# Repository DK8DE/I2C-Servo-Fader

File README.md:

# I2C-Servo-Fader 

> [!CAUTION]
> The project is not yet complete. I am still waiting for the faders and the PCBs. Only then can I finish writing the code for the fader. The code still lacks the motor control in relation to the fader track.
## Description
This project consists of a board for a motor fader, the code for the microcontroller on the board, and a library to control this fader with an Arduino or an ESP32. The compatible faders are:
+ Behringer X-Touch Motor-Fader MF100T
+ Soundwell SM10001NKA0X-HA1
+ RSA0N11M9A07

Of course, the board can also be adapted for other faders by adjusting the footprint.

### Connections on the Board:
* SDA
* SCL
* +5V for the microcontroller
* 8-10V for the motor
* 1x interrupt pin
* 1x Opt button
* 1x Neo-Pixel-LED
* 1x UPDI

All signals are looped through on the board. This means that several boards can be placed next to each other and easily connected to each other.

## Funktion
The board also has the option to control a NeoPixel LED and an additional button. The NeoPixel LED can be fully controlled via the I2C bus, including RGB color, on, off, and brightness. This allows, for example, changing the color based on the set level or displaying notifications.
The fader has a touch function that can also be evaluated and is internally used to trigger an interrupt. You only need to check when the interrupt line is pulled LOW.
The optional button input can be queried and also triggers an interrupt when pressed.
The interrupt is only reset when the value on the fader that caused the interrupt is read. This ensures that no unnecessary queries are made and no changes are lost.
In the example code, the interrupt line is connected to a pin on the microcontroller that can also trigger an interrupt. This ensures that the microcontroller responds immediately to changes. On an Arduino UNO or Nano, pins 2 and 3 can be used.
To set an I2C address for the fader, you need to connect to the fader using the serial console and simply enter the address in the format 0x08. The address is then stored in ROM and used on the next startup. In theory, you can operate 127 faders on one bus ;-).
The functions of the library are thoroughly documented in I2cServoFader.h, and all functions are used in the example code. The example code also shows how to control multiple sliders.

# Example Code Description
This example code demonstrates how to control I2C servo sliders using an Arduino. The code supports one slider and can be extended to two sliders by uncommenting the relevant sections. The sliders can be controlled via serial commands, and their positions and LED colors can be adjusted based on analog values.

### Serial Commands:
+ sliderpos1=<value>: Sets the position of slider 1 to the specified value (0-255).
+ sliderpos2=<value>: Sets the position of slider 2 to the specified value (0-255).
+ slidertest=1: Initiates a demonstration of slider 1's movement through a series of positions.
+ slidertest=2: Initiates a demonstration of slider 2's movement through a series of positions.

### Interrupt Handling:
When an interrupt occurs, the code reads the analog value and optio state from the sliders, prints these values to the serial console, and updates the LED colors based on the analog values.
The interrupt is triggered by a change in the state of the connected pin (e.g., pin 2).

### LED Color Representation:
+ Green (analog value = 0)
+ Yellow (analog value ≈ 128)
+ Red (analog value = 255)
The LED color transitions smoothly between these values based on the analog value.
# Sources
Part of the circuit board layout is from this project:
https://github.com/GadgetReboot/PSM60_Fader_Controller

# Partlist
This is the BOM. If you don't buy the faders in Germany but from the friendly Chinese, they cost about 12€ per piece.
You can find them on AliExpress here: [RSA0N11M9A0J](https://de.aliexpress.com/item/1005006910254678.html).

| Part | Value | Package | PART_NUMBER | Price €|
|:--- |:--- |:--- |:--- |:--- |
| C1 | 100nF | C0805 | C0805C104K1RACTU | 0.16 | 
| C2 | 10nF | C0805 | C0805Y103K4RACTU | 0.16 |
| C3 | 100nF | C0805 | C0805C104K1RACTU | 0.16 |
| C4 | 22nF | C0805 | C0805C223K5RAC7210 | 0.09|
| C5 | 10uF | T491A | T491A106M016AT7280 | 0.35 |
| C6 | 10uF | T491A | T491A106M016AT7280 | 0.35 |
| C7 | 10uF | T491A | T491A106M016AT7280 | 0.35 |
| C8 | 100nF | C0805 | C0805C104K1RACTU | 0.16 |
| C9 | 100nF | C0805 | C0805C104K1RACTU | 0.16 |
| FADER | MF100T | SM10001NKA0X-HA1 |  | 20.00|
| IC1 | ATTINY1604-SSN | SOIC127P600X175-14N | ATTINY1604-SSN | 0.70|
| IC2 | AT42QT1010 | SOT95P280X145-6N | AT42QT1010-TSHR | 0.72|
| IC4 | SN74LVC1G14DBVR | SOT95P280X145-5N | SN74LVC1G14DBVR | 0.20 |
| IC5 | TB6612FNG,C,8,EL | SOP65P760X160-24N | TB6612FNG,C,8,EL | 1.35 |
| LED1 | 150080GS75000 | LEDM2012X80N | 150080GS75000 | 0.18 |
| LED2 | 150080GS75000 | LEDM2012X80N | 150080GS75000 | 0.18 |
| LED3 | 150080YS75000 | LEDC2012X80N | 150080YS75000 | 0.18 |
| R1 | 0R | R0805 | OPT | 0.08 |
| R2 | 1K | R0805 | | 0.08 |
| R3 | 470R | R0805 | | 0.08 | 
| R4 | 10K | R0805 | | 0.08 |
| R5 | 1K | R0805 | | 0.08 |
| R6 | 1K | R0805 | | 0.08 |
| SV1 | 0 | MA06-1 | | 0.15 |
| SV2 | 0 | MA06-1 | | 0.15 |
| SV3 | 0 | MA03-1 | | 0.15 |
| SV4 | 0 | MA03-1 | | 0.15 |
| SV5 | 22-23-2021 | 22-23-2021 | | 0.20 |
| PCB ||||2.00|
|T-Lever |||| 1.25 |
|Total |||| ~ 28.00€ |

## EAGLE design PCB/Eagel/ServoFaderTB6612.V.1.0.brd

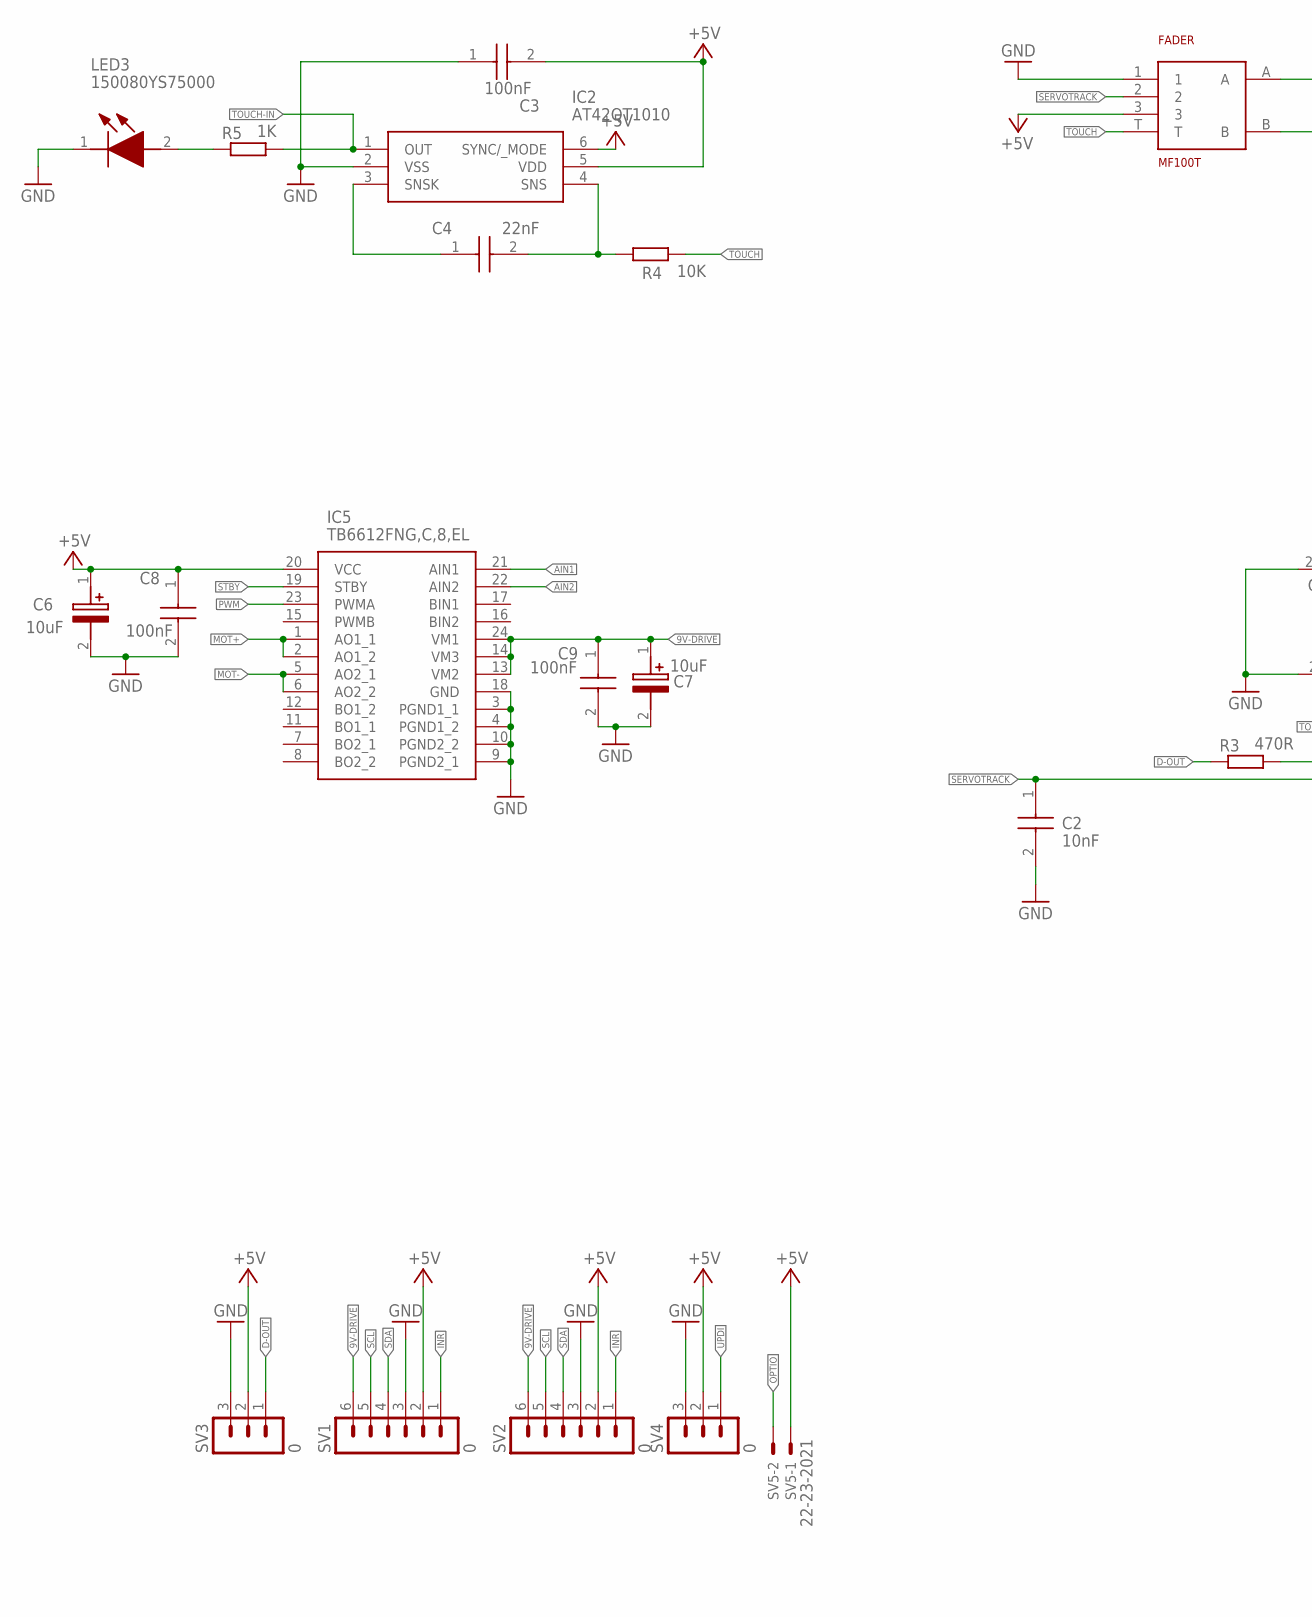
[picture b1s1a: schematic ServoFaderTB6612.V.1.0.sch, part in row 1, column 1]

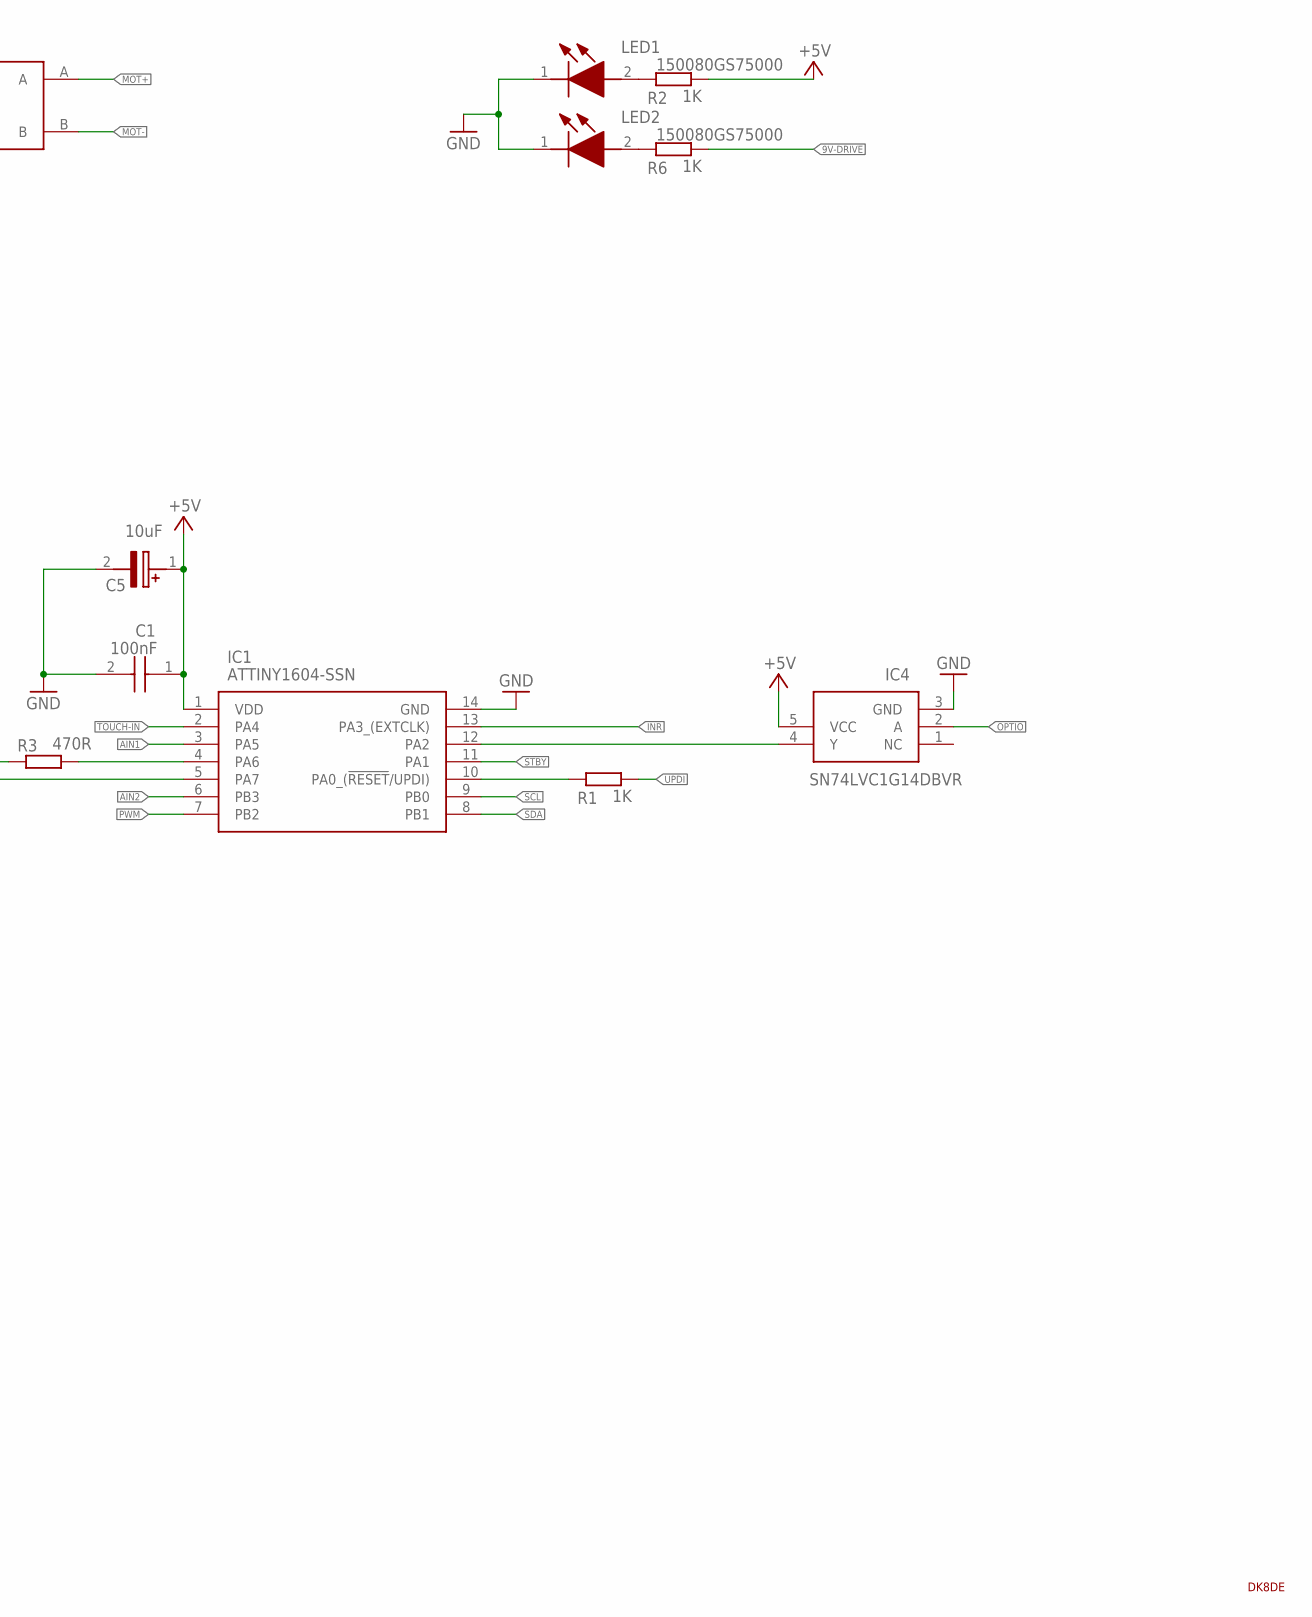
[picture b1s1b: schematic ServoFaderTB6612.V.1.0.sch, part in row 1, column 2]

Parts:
C1, C3, C8, C9: 100nF; C0805
C2: 10nF; C0805
C4: 22nF; C0805
C5, C6, C7: 10uF; T491A
FADER: MF100T; SM10001NKA0X-HA1
IC1: ATTINY1604-SSN; SOIC127P600X175-14N
IC2: AT42QT1010; SOT95P280X145-6N
IC4: SN74LVC1G14DBVR; SOT95P280X145-5N
IC5: TB6612FNG,C,8,EL; SOP65P760X160-24N
LED1, LED2: 150080GS75000; LEDM2012X80N
LED3: 150080YS75000; LEDC2012X80N
LOGO: DK8DESS; DK8DE_KLEIN
R1, R2, R5, R6: 1K; R0805
R3: 470R; R0805
R4: 10K; R0805
SV1, SV2: 0; MA06-1
SV3, SV4: 0; MA03-1
SV5: 22-23-2021

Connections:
9V-DRIVE: C7.1 (+), C9.1, IC5.13 (VM2), IC5.14 (VM3), IC5.24 (VM1), R6.2, SV1.6, SV2.6
+5V: C1.1, C3.2, C5.1 (+), C6.1 (+), C8.1, FADER.3, IC1.1 (VDD), IC2.5 (VDD), IC2.6 (SYNC/_MODE), IC4.5 (VCC), IC5.20 (VCC), R2.2, SV1.2, SV2.2, SV3.2, SV4.2, SV5.1
AIN1: IC1.3 (PA5), IC5.21 (AIN1)
AIN2: IC1.6 (PB3), IC5.22 (AIN2)
D-OUT: R3.1, SV3.1
GND: C1.2, C2.2, C3.1, C5.2 (-), C6.2 (-), C7.2 (-), C8.2, C9.2, FADER.1, IC1.14 (GND), IC2.2 (VSS), IC4.3 (GND), IC5.3 (PGND1_1), IC5.4 (PGND1_2), IC5.9 (PGND2_1), IC5.10 (PGND2_2), IC5.18 (GND), LED1.1 (K), LED2.1 (K), LED3.1 (K), SV1.3, SV2.3, SV3.3, SV4.3
INR: IC1.13 (PA3_(EXTCLK)), SV1.1, SV2.1
MOT+: FADER.A, IC5.1 (AO1_1), IC5.2 (AO1_2)
MOT-: FADER.B, IC5.5 (AO2_1), IC5.6 (AO2_2)
unnamed: IC1.10 (PA0_(!RESET!/UPDI)), R1.1
unnamed: LED1.2 (A), R2.1
unnamed: LED2.2 (A), R6.1
unnamed: IC1.12 (PA2), IC4.4 (Y)
unnamed: IC1.4 (PA6), R3.2
unnamed: C4.1, IC2.3 (SNSK)
unnamed: C4.2, IC2.4 (SNS), R4.1
unnamed: LED3.2 (A), R5.1
OPTIO: IC4.2 (A), SV5.2
PWM: IC1.7 (PB2), IC5.23 (PWMA)
SCL: IC1.9 (PB0), SV1.5, SV2.5
SDA: IC1.8 (PB1), SV1.4, SV2.4
SERVOTRACK: C2.1, FADER.2, IC1.5 (PA7)
STBY: IC1.11 (PA1), IC5.19 (STBY)
TOUCH: FADER.T, R4.2
TOUCH-IN: IC1.2 (PA4), IC2.1 (OUT), R5.2
UPDI: R1.2, SV4.1

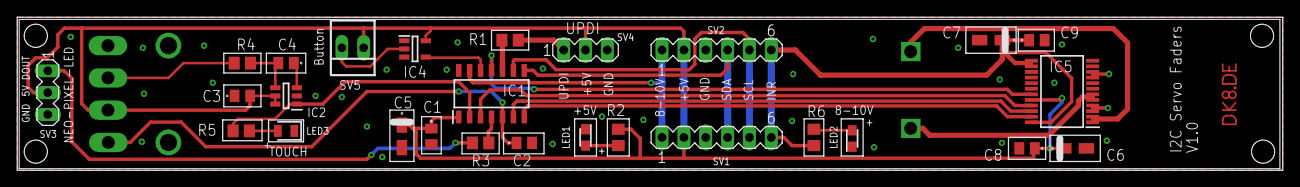
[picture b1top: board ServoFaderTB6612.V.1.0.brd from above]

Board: 2 copper layers, 147.1 x 17.8 mm, 29 parts (0 on the bottom side), 26 nets.

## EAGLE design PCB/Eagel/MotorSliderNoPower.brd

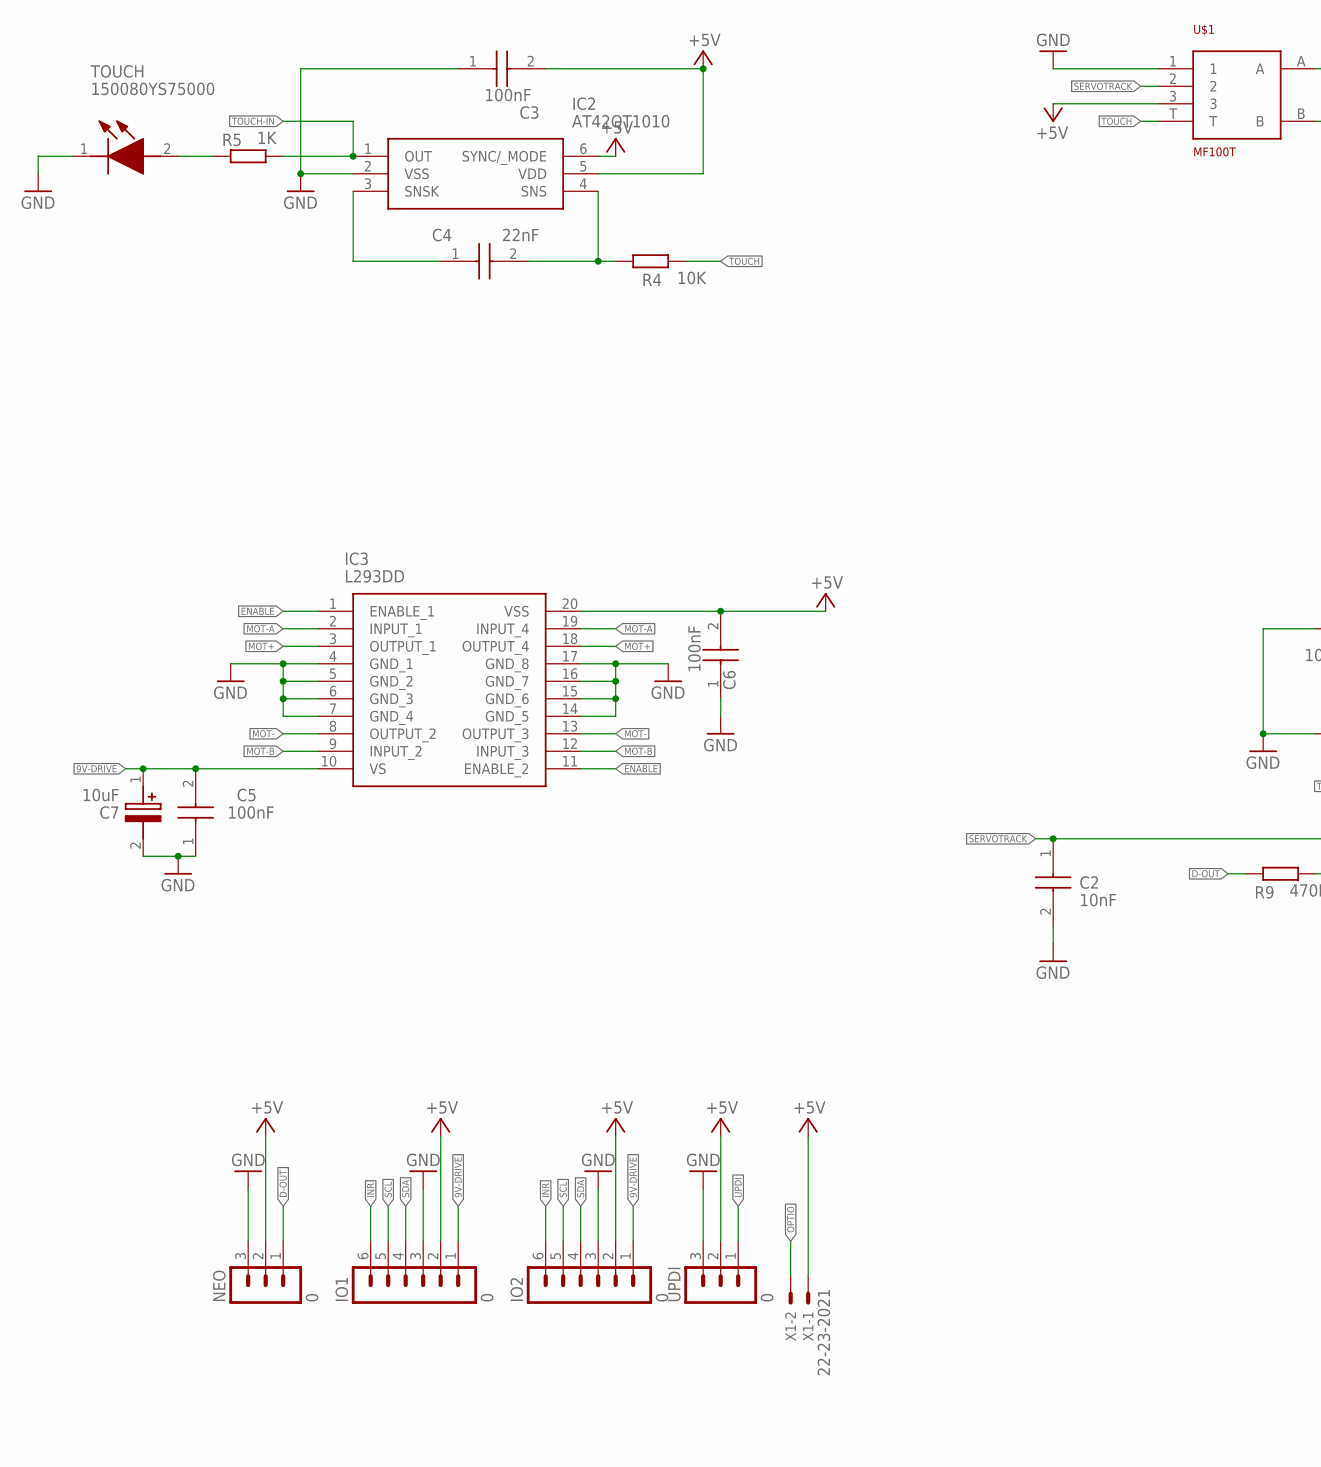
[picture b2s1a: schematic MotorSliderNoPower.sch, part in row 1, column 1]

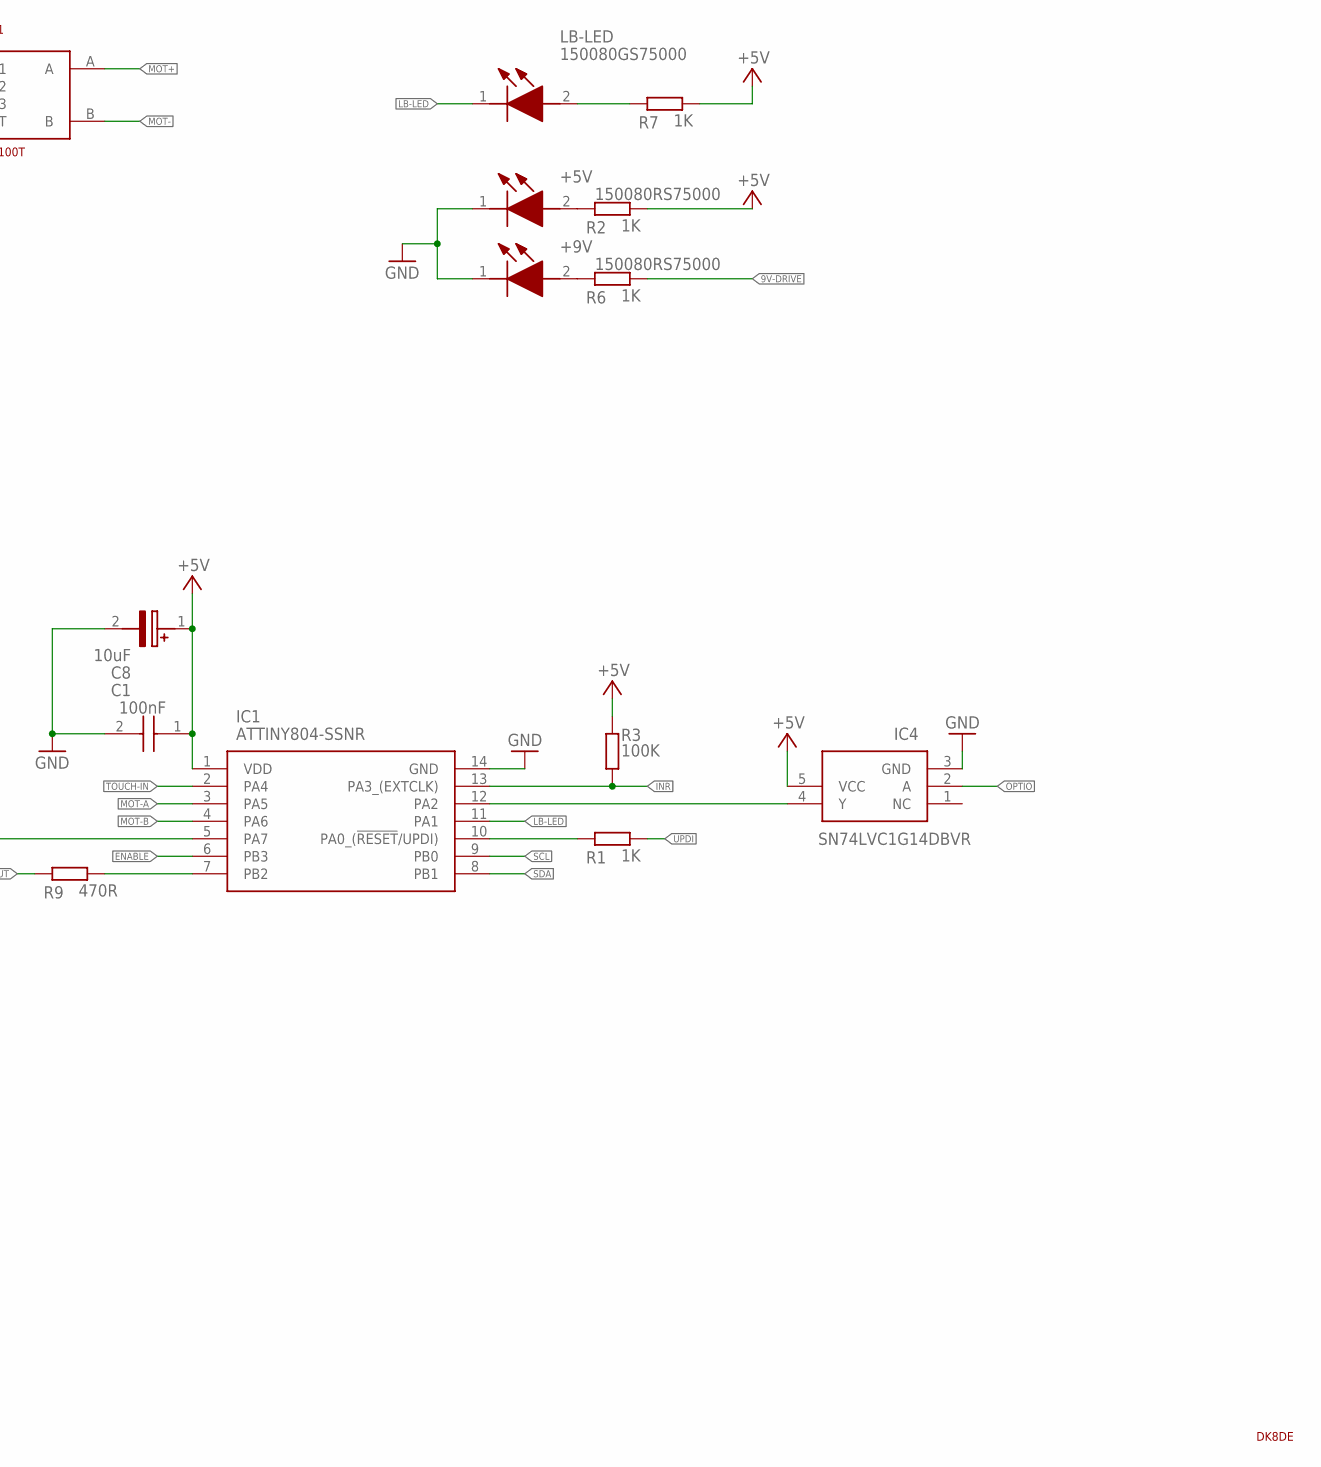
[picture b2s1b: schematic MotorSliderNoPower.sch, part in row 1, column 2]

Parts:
+5V, +9V: 150080RS75000; LEDC2012X80N
C1, C3, C5, C6: 100nF; C0805
C2: 10nF; C0805
C4: 22nF; C0805
C7, C8: 10uF; EEE1AA220WR
IC1: ATTINY804-SSNR; SOIC127P600X175-14N
IC2: AT42QT1010; SOT95P280X145-6N
IC3: L293DD; SOIC127P1032X265-20N
IC4: SN74LVC1G14DBVR; SOT95P280X145-5N
IO1, IO2: 0; MA06-1
LB-LED: 150080GS75000; LEDM2012X80N
NEO: 0; MA03-1
R1, R2, R5, R6, R7: 1K; R0805
R3: 100K; R0805
R4: 10K; R0805
R9: 470R; R0805
TOUCH: 150080YS75000; LEDC2012X80N
U$1: MF100T; SM10001NKA0X-HA1
U$2: DK8DESS; DK8DE_KLEIN
UPDI: 0; MA03-1
X1: 22-23-2021

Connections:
9V-DRIVE: C5.2, C7.1 (+), IC3.10 (VS), IO1.1, IO2.1, R6.2
+5V: C1.1, C3.2, C6.2, C8.1 (+), IC1.1 (VDD), IC2.5 (VDD), IC2.6 (SYNC/_MODE), IC3.20 (VSS), IC4.5 (VCC), IO1.2, IO2.2, NEO.2, R2.2, R3.1, R7.2, U$1.3, UPDI.2, X1.1
D-OUT: NEO.1, R9.1
ENABLE: IC1.6 (PB3), IC3.1 (ENABLE_1), IC3.11 (ENABLE_2)
GND: +5V.1 (K), +9V.1 (K), C1.2, C2.2, C3.1, C5.1, C6.1, C7.2 (-), C8.2 (-), IC1.14 (GND), IC2.2 (VSS), IC3.4 (GND_1), IC3.5 (GND_2), IC3.6 (GND_3), IC3.7 (GND_4), IC3.14 (GND_5), IC3.15 (GND_6), IC3.16 (GND_7), IC3.17 (GND_8), IC4.3 (GND), IO1.3, IO2.3, NEO.3, TOUCH.1 (K), U$1.1, UPDI.3
INR: IC1.13 (PA3_(EXTCLK)), IO1.6, IO2.6, R3.2
LB-LED: IC1.11 (PA1), LB-LED.1 (K)
MOT+: IC3.3 (OUTPUT_1), IC3.18 (OUTPUT_4), U$1.A
MOT-: IC3.8 (OUTPUT_2), IC3.13 (OUTPUT_3), U$1.B
MOT-A: IC1.3 (PA5), IC3.2 (INPUT_1), IC3.19 (INPUT_4)
MOT-B: IC1.4 (PA6), IC3.9 (INPUT_2), IC3.12 (INPUT_3)
unnamed: IC1.10 (PA0_(!RESET!/UPDI)), R1.1
unnamed: +5V.2 (A), R2.1
unnamed: +9V.2 (A), R6.1
unnamed: IC1.12 (PA2), IC4.4 (Y)
unnamed: LB-LED.2 (A), R7.1
unnamed: IC1.7 (PB2), R9.2
unnamed: C4.1, IC2.3 (SNSK)
unnamed: C4.2, IC2.4 (SNS), R4.1
unnamed: R5.1, TOUCH.2 (A)
OPTIO: IC4.2 (A), X1.2
SCL: IC1.9 (PB0), IO1.5, IO2.5
SDA: IC1.8 (PB1), IO1.4, IO2.4
SERVOTRACK: C2.1, IC1.5 (PA7), U$1.2
TOUCH: R4.2, U$1.T
TOUCH-IN: IC1.2 (PA4), IC2.1 (OUT), R5.2
UPDI: R1.2, UPDI.1

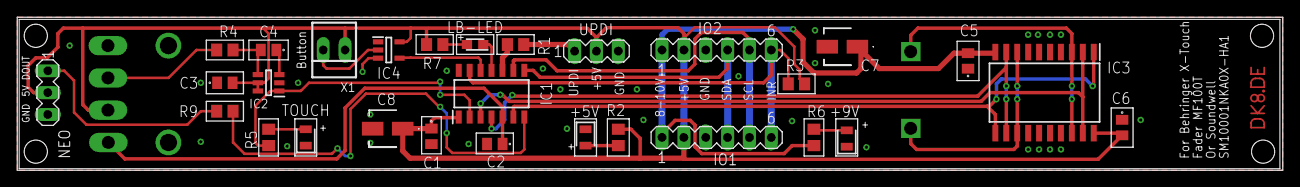
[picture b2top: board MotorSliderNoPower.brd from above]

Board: 2 copper layers, 147.1 x 17.8 mm, 31 parts (0 on the bottom side), 27 nets.

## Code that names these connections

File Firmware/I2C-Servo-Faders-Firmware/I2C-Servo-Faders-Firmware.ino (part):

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#define EEPROM_I2C_ADDRESS 0      //!< EEPROM address for storing the I2C address
#define NEOPIXEL_PIN 4            //!< Data pin for the NeoPixel LED
#define NUMPIXELS 1               //!< Number of LEDs
#define STBY 7                    //!< Standby pin
#define ANALOG_PIN A0             //!< Pin for analogRead
#define TOUCH_PIN 2               //!< Signal from the touch controller when the button is touched
#define INTERRUPT 8               //!< Pin opposite to TOUCH_PIN
#define PWM_PIN 3                 //!< Pin for PWM signal
#define DIR_PIN1 9                //!< Pin for motor direction
#define DIR_PIN2 10               //!< Pin for motor direction
#define OPTIO_PIN 11              //!< Optional IO pin

Adafruit_NeoPixel pixels(NUMPIXELS, NEOPIXEL_PIN, NEO_GRB + NEO_KHZ800);

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  REGISTER_BRIGHTNESS,      //!< Register for setting the brightness value
  REGISTER_ANALOG_VALUE,    //!< Register for reading the analog value
  REGISTER_TOUCH,           //!< Register for reading the touch state
  REGISTER_OPTIO_READ,      //!< Register for reading the state of OPTIO_PIN
  REGISTER_SET_POSITION,    //!< Register for setting the target position of the servo
  REGISTER_COUNT            //!< Total number of registers
};
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  // Initialize the analog pin
  pinMode(ANALOG_PIN, INPUT);

  // Initialize the STBY pin
  pinMode(STBY, OUTPUT);
  digitalWrite(STBY, LOW); // Default state

  // Initialize the TOUCH_PIN and INTERRUPT_PIN
  pinMode(TOUCH_PIN, INPUT);
  pinMode(INTERRUPT, OUTPUT);
  digitalWrite(INTERRUPT, HIGH); // Default value for INTERRUPT_PIN

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  pinMode(DIR_PIN1, OUTPUT);
  pinMode(DIR_PIN2, OUTPUT);

  // Initialize the OPTIO_PIN
  pinMode(OPTIO_PIN, INPUT_PULLUP);

  // Default state of the motor
  stopMotor();
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  // Regularly update the analog value
  updateAnalogValue();

  // Check the state of the OPTIO_PIN
  if (digitalRead(OPTIO_PIN) == LOW) {
    if (!optioOccurred) {
      registers[REGISTER_OPTIO_READ] = 1;
      optioOccurred = true;
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    registers[REGISTER_OPTIO_READ] = 0;
  }

  // Check the state of the TOUCH_PIN
  if (digitalRead(TOUCH_PIN) == LOW) {
    if (!touchOccurred) {
      registers[REGISTER_TOUCH] = 1;
      touchOccurred = true;
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
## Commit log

2024-06-11 0.1
    Noch ohne Motoransteuerung Beta
2024-06-11 Serial Fix
2024-06-12 Dateinamen gändert
2024-06-12 update image
2024-06-12 Add STBY Pin
2024-06-12 Update Pin PB3
2024-06-13 Update
    Motorsteuerung mit ABS eingefügt
2024-06-13 Upload
2024-07-04 V2.0
